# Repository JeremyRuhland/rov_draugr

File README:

5x h bridges
    4 input         =   20 input
                        3x 8-bit shift registers w/ spi interface
                                5 gpio: miso, mosi, sck, latch, cs
    1 output        =   5 outputs
    1 analog        =   5 analog
        
spi arm interface   =   spi interface
                        4 gpio: miso, mosi, sck, cs

conductivity sensor =   1 analog

temp sensing        =   4 analog

range finder        =   ? 
                        4 gpio

USB interface       =   1 input
                        1 interupt

-------------------------------------------------------------------------------

3 spi
2 uart for poolside comms: rx, tx
1 gpio for usb: +
1 interupt for usb: -
2 gpio for h bridge shift registers: latch, cs
5 gpio for h bridge status
5 adc for h bridge current draw
1 gpio for arm interface: cs
1 adc for water conductivity sensor
2 adc for heat pipe thermal monitors
?1 gpio for range finder: cs

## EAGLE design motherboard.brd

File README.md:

Western Washington University Marine Technology Club 2014 ROV: Draugr
=====================================================================

More information can be found on my [WWU MTC page](http://goopypanther.org/seniorProjectWebsite/wwu-marine-technology-club.html) or the [main blog post](http://blog.goopypanther.org/posts/ROV_Project:_Draugr/) about Draugr.

The stuff here's pretty old and probably doesn't reflect the current state of the ROV. Some firmware tweaks may have been made last minute in responce to hardware changes. Only the basic functionality was fully implemented and tested.

You can control the ROV via a screen session and the keyboard, the actual GUI that uses the xbox controller was written by Sean and got stored elsewhere (somewhere?).

File hierarchy
--------------

 * firmware
  * C source files
 * hardware
  * Schematics and gerbers for main control board
 * protocol_documentation
  * Command protocol for designing control software

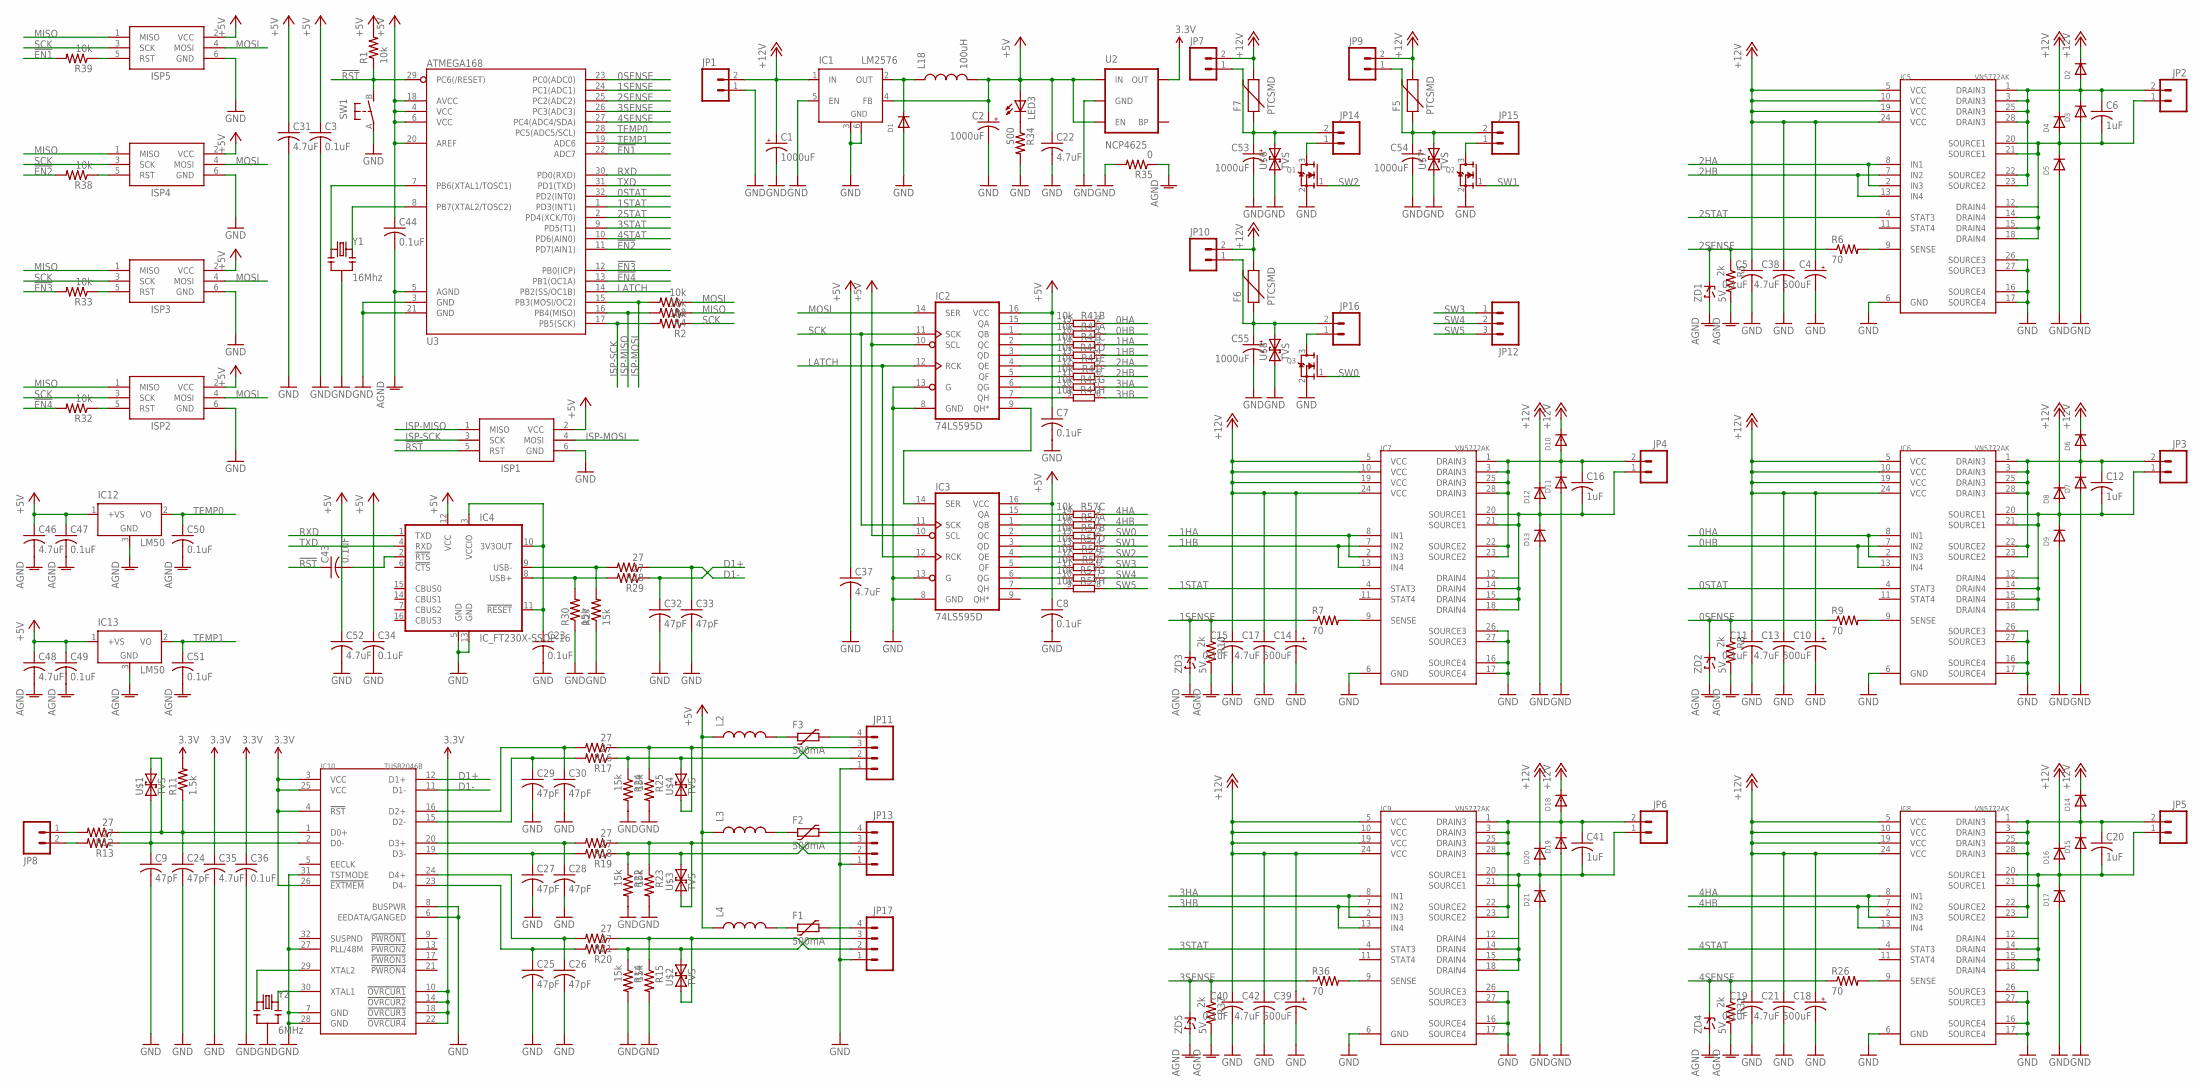
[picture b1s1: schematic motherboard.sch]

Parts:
C1, C2, C53, C54, C55: 1000uF; 153CLV-0807
C3, C5, C7, C8, C11, C15, C19, C23, C34, C36, C40, C43, C44, C47, C49, C50, C51: 0.1uF; C1206
C4, C10, C14, C18, C39: 500uF; 153CLV-0807
C6, C12, C16, C20, C41: 1uF; C1206
C9, C24, C25, C26, C27, C28, C29, C30, C32, C33: 47pF; C1206
C13, C17, C21, C22, C31, C35, C37, C38, C42, C46, C48, C52: 4.7uF; C1206
D1: DIODESMA; SMADIODE
D2, D3, D4, D5, D6, D7, D8, D9, D10, D11, D12, D13, D14, D15, D16, D17, D18, D19, D20, D21: DIODESOD-123; SOD-123
F1, F2, F3: 500mA; PTC1812L
F5, F6, F7: PTCSMD; PTC-1206
IC1: LM2576; TO263-5
IC2, IC3: 74LS595D; SO16
IC4: IC_FT230X-SSOP-16; SSOP-16-FTDI
IC5, IC6, IC7, IC8, IC9: VN5772AK; SO-28
IC10: TUSB2046B; LQFP-32
IC12, IC13: LM50; SOT23
ISP1, ISP2, ISP3, ISP4, ISP5: AVRISP-6; AVRISP
JP1, JP2, JP3, JP4, JP5, JP6, JP8, JP14, JP15, JP16: M023.5MM; SCREWTERMINAL-3.5MM-2
JP7, JP9, JP10: M02PTH; 1X02
JP11, JP13, JP17: M04SCREW; SCREWTERMINAL-3.5MM-4
JP12: M03PTH; 1X03
L2, L3, L4: INDUCTOR1206H*; INDUCTOR-1206
L18: 100uH; CDRH125
LED3: LEDCHIPLED_1206; CHIPLED_1206
Q1, Q2, Q3: MOSFET-NREFLOW; SOT23
R1, R2, R3, R4, R32, R33, R38, R39: 10k; R1206
R5, R8, R10, R31, R37: 2k; R1206
R6, R7, R9, R26, R36: 70; R1206
R11: 1.5k; R1206
R12, R13, R16, R17, R18, R19, R20, R21, R28, R29: 27; R1206
R14, R15, R22, R23, R24, R25, R27, R30: 15k; R1206
R34: 500; R1206
R35: 0; R1206
R41, R57: 10k; SO16
SW1: FSMSM
U2: NCP4625; SOT23-5
U3: ATMEGA168; TQFP32-08
U$1, U$2, U$3, U$4, U$6, U$7, U$8: TVS; SMA-DIODE
Y1: 16Mhz; RESONATOR-SMD
Y2: 6MHz; RESONATOR-SMD
ZD1, ZD2, ZD3, ZD4, ZD5: 5V; SOD-123

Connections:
0HA: IC6.2 (IN3), IC6.8 (IN1), R41.2 (1)
0HB: IC6.7 (IN2), IC6.13 (IN4), R41.1
0SENSE: R8.1, R9.1, U3.23 (PC0(ADC0)), ZD2.C
0STAT: IC6.4 (STAT3), U3.32 (PD2(INT0))
1HA: IC7.2 (IN3), IC7.8 (IN1), R41.3 (1)
1HB: IC7.7 (IN2), IC7.13 (IN4), R41.4 (1)
1SENSE: R7.1, R10.1, U3.24 (PC1(ADC1)), ZD3.C
1STAT: IC7.4 (STAT3), U3.1 (PD3(INT1))
2HA: IC5.2 (IN3), IC5.8 (IN1), R41.5 (1)
2HB: IC5.7 (IN2), IC5.13 (IN4), R41.6 (1)
2SENSE: R5.1, R6.1, U3.25 (PC2(ADC2)), ZD1.C
2STAT: IC5.4 (STAT3), U3.2 (PD4(XCK/T0))
3.3V: C35.1, C36.1, IC10.3 (VCC), IC10.4 (!RST), IC10.10 (!OVRCUR1), IC10.14 (!OVRCUR2), IC10.18 (!OVRCUR3), IC10.22 (!OVRCUR4), IC10.25 (VCC), IC10.26 (!EXTMEM), R11.2, U2.5 (OUT)
3HA: IC9.2 (IN3), IC9.8 (IN1), R41.7 (1)
3HB: IC9.7 (IN2), IC9.13 (IN4), R41.8 (1)
3SENSE: R36.1, R37.1, U3.26 (PC3(ADC3)), ZD5.C
3STAT: IC9.4 (STAT3), U3.9 (PD5(T1))
4HA: IC8.2 (IN3), IC8.8 (IN1), R57.3 (1)
4HB: IC8.7 (IN2), IC8.13 (IN4), R57.1
4SENSE: R26.1, R31.1, U3.27 (PC4(ADC4/SDA)), ZD4.C
4STAT: IC8.4 (STAT3), U3.10 (PD6(AIN0))
!EN1: R39.2, U3.22 (ADC7)
!EN2: R38.2, U3.11 (PD7(AIN1))
!EN3: R33.2, U3.12 (PB0(ICP))
!EN4: R32.2, U3.13 (PB1(OC1A))
!RST: C43.1, ISP1.5 (RST), R1.1, SW1.B (S), U3.29 (PC6(/RESET))
+5V: C2.+, C3.1, C7.1, C8.1, C22.1, C31.1, C34.1, C37.1, C44.1, C46.1, C47.1, C48.1, C49.1, C52.1, IC1.4 (FB), IC2.10 (SCL), IC2.16 (VCC), IC3.10 (SCL), IC3.16 (VCC), IC4.12 (VCC), IC12.1 (+VS), IC13.1 (+VS), ISP1.2 (VCC), ISP2.2 (VCC), ISP3.2 (VCC), ISP4.2 (VCC), ISP5.2 (VCC), L2.P$1 (1), L3.P$1 (1), L4.P$1 (1), L18.2, LED3.A, R1.2, U2.1 (IN), U2.3 (EN), U3.4 (VCC), U3.6 (VCC), U3.18 (AVCC), U3.20 (AREF)
+12V: C1.+, C4.+, C5.1, C10.+, C11.1, C13.1, C14.+, C15.1, C17.1, C18.+, C19.1, C21.1, C38.1, C39.+, C40.1, C42.1, D2.C, D4.C, D6.C, D8.C, D10.C, D12.C, D14.C, D16.C, D18.C, D20.C, F5.2, F6.2, F7.2, IC1.1 (IN), IC5.5 (VCC), IC5.10 (VCC), IC5.19 (VCC), IC5.24 (VCC), IC6.5 (VCC), IC6.10 (VCC), IC6.19 (VCC), IC6.24 (VCC), IC7.5 (VCC), IC7.10 (VCC), IC7.19 (VCC), IC7.24 (VCC), IC8.5 (VCC), IC8.10 (VCC), IC8.19 (VCC), IC8.24 (VCC), IC9.5 (VCC), IC9.10 (VCC), IC9.19 (VCC), IC9.24 (VCC), JP1.2, JP7.2, JP9.2, JP10.2; also elsewhere on the board
AGND: C44.2, C46.2, C47.2, C48.2, C49.2, C50.2, C51.2, IC12.3 (GND), IC13.3 (GND), R5.2, R8.2, R10.2, R31.2, R35.1, R37.2, U3.5 (AGND), ZD1.A, ZD2.A, ZD3.A, ZD4.A, ZD5.A
D1+: C32.1, IC10.12 (D1+), R29.1
D1-: C33.1, IC10.11 (D1-), R28.1
GND: C1.-, C2.-, C3.2, C4.-, C5.2, C7.2, C8.2, C9.2, C10.-, C11.2, C13.2, C14.-, C15.2, C17.2, C18.-, C19.2, C21.2, C22.2, C23.2, C24.2, C25.2, C26.2, C27.2, C28.2, C29.2, C30.2, C31.2, C32.2, C33.2, C34.2, C35.2, C36.2, C37.2, C38.2, C39.-, C40.2, C42.2, C52.2, C53.-, C54.-, C55.-, D1.A, D3.A, D5.A, D7.A, D9.A, D11.A, D13.A, D15.A, D17.A, D19.A, D21.A, IC1.3 (GND), IC1.5 (EN), IC1.6 (GND), IC2.8 (GND), IC2.13 (G), IC3.8 (GND), IC3.13 (G), IC4.5 (GND), IC4.13 (GND), IC5.6 (GND), IC5.16 (SOURCE4), IC5.17 (SOURCE4), IC5.26 (SOURCE3), IC5.27 (SOURCE3), IC6.6 (GND), IC6.16 (SOURCE4), IC6.17 (SOURCE4), IC6.26 (SOURCE3), IC6.27 (SOURCE3), IC7.6 (GND), IC7.16 (SOURCE4), IC7.17 (SOURCE4), IC7.26 (SOURCE3), IC7.27 (SOURCE3), IC8.6 (GND), IC8.16 (SOURCE4), IC8.17 (SOURCE4), IC8.26 (SOURCE3), IC8.27 (SOURCE3), IC9.6 (GND), IC9.16 (SOURCE4), IC9.17 (SOURCE4), IC9.26 (SOURCE3), IC9.27 (SOURCE3), IC10.6 (EEDATA/GANGED), IC10.7 (GND), IC10.8 (BUSPWR), IC10.27 (PLL/48M), IC10.28 (GND), IC10.31 (TSTMODE), ISP1.6 (GND), ISP2.6 (GND), ISP3.6 (GND), ISP4.6 (GND), ISP5.6 (GND), JP1.1, JP11.1, JP13.1, JP17.1, Q1.2 (S), Q2.2 (S), Q3.2 (S), R14.2, R15.2, R22.2, R23.2, R24.2, R25.2, R27.1, R30.1, R34.2, R35.2, SW1.A, U2.2 (GND), U3.3 (GND), U3.21 (GND), U$6.A (1), U$7.A (1), U$8.A (1), Y1.2, Y2.2
ISP-MISO: ISP1.1 (MISO), R4.2, U3.16 (PB4(MISO))
ISP-MOSI: ISP1.4 (MOSI), R3.2, U3.15 (PB3(MOSI/OC2))
ISP-SCK: ISP1.3 (SCK), R2.2, U3.17 (PB5(SCK))
LATCH: IC2.12 (RCK), IC3.12 (RCK), U3.14 (PB2(SS/OC1B))
MISO: ISP2.1 (MISO), ISP3.1 (MISO), ISP4.1 (MISO), ISP5.1 (MISO), R4.1
MOSI: IC2.14 (SER), ISP2.4 (MOSI), ISP3.4 (MOSI), ISP4.4 (MOSI), ISP5.4 (MOSI), R3.1
unnamed: D1.C, IC1.2 (OUT), L18.1
unnamed: U3.8 (PB7(XTAL2/TOSC2)), Y1.3
unnamed: C12.2, D8.A, D9.C, IC6.12 (DRAIN4), IC6.14 (DRAIN4), IC6.15 (DRAIN4), IC6.18 (DRAIN4), IC6.20 (SOURCE1), IC6.21 (SOURCE1), JP3.1
unnamed: U3.7 (PB6(XTAL1/TOSC1)), Y1.1
unnamed: C12.1, D6.A, D7.C, IC6.1 (DRAIN3), IC6.3 (DRAIN3), IC6.22 (SOURCE2), IC6.23 (SOURCE2), IC6.25 (DRAIN3), IC6.28 (DRAIN3), JP3.2
unnamed: IC2.9 (QH*), IC3.14 (SER)
unnamed: C9.1, IC10.2 (D0-), R13.1, U$1.A (1)
unnamed: C16.2, D12.A, D13.C, IC7.12 (DRAIN4), IC7.14 (DRAIN4), IC7.15 (DRAIN4), IC7.18 (DRAIN4), IC7.20 (SOURCE1), IC7.21 (SOURCE1), JP4.1
unnamed: C16.1, D10.A, D11.C, IC7.1 (DRAIN3), IC7.3 (DRAIN3), IC7.22 (SOURCE2), IC7.23 (SOURCE2), IC7.25 (DRAIN3), IC7.28 (DRAIN3), JP4.2
unnamed: C20.2, D16.A, D17.C, IC8.12 (DRAIN4), IC8.14 (DRAIN4), IC8.15 (DRAIN4), IC8.18 (DRAIN4), IC8.20 (SOURCE1), IC8.21 (SOURCE1), JP5.1
unnamed: C20.1, D14.A, D15.C, IC8.1 (DRAIN3), IC8.3 (DRAIN3), IC8.22 (SOURCE2), IC8.23 (SOURCE2), IC8.25 (DRAIN3), IC8.28 (DRAIN3), JP5.2
unnamed: C41.2, D20.A, D21.C, IC9.12 (DRAIN4), IC9.14 (DRAIN4), IC9.15 (DRAIN4), IC9.18 (DRAIN4), IC9.20 (SOURCE1), IC9.21 (SOURCE1), JP6.1
unnamed: C6.2, D4.A, D5.C, IC5.12 (DRAIN4), IC5.14 (DRAIN4), IC5.15 (DRAIN4), IC5.18 (DRAIN4), IC5.20 (SOURCE1), IC5.21 (SOURCE1), JP2.1
unnamed: C41.1, D18.A, D19.C, IC9.1 (DRAIN3), IC9.3 (DRAIN3), IC9.22 (SOURCE2), IC9.23 (SOURCE2), IC9.25 (DRAIN3), IC9.28 (DRAIN3), JP6.2
unnamed: IC3.7 (QH), R57.9 (2)
unnamed: C43.2, IC4.2 (!RTS)
unnamed: IC3.6 (QG), R57.10 (2)
unnamed: IC3.5 (QF), R57.11 (2)
unnamed: C24.1, IC10.1 (D0+), R11.1, R12.1, U$1.C (2)
unnamed: JP17.2, R15.1, R21.1, U$2.A (1)
unnamed: IC10.30 (XTAL1), Y2.3
unnamed: IC10.29 (XTAL2), Y2.1
unnamed: JP17.3, R14.1, R20.1, U$2.C (2)
unnamed: JP13.3, R19.1, R22.1, U$3.C (2)
unnamed: C30.1, IC10.16 (D2+), R16.2
unnamed: C29.1, IC10.15 (D2-), R17.2
unnamed: C28.1, IC10.20 (D3+), R18.2
unnamed: C27.1, IC10.19 (D3-), R19.2
unnamed: C25.1, IC10.23 (D4-), R20.2
unnamed: C26.1, IC10.24 (D4+), R21.2
unnamed: JP13.2, R18.1, R23.1, U$3.A (1)
unnamed: JP11.3, R17.1, R24.1, U$4.C (2)
unnamed: JP11.2, R16.1, R25.1, U$4.A (1)
unnamed: F1.2, JP17.4
unnamed: F2.2, JP13.4
unnamed: F3.2, JP11.4
unnamed: C23.1, IC4.3 (VCCIO), IC4.10 (3V3OUT), IC4.11 (!RESET)
unnamed: IC4.9 (USB-), R27.2, R28.2
unnamed: IC4.8 (USB+), R29.2, R30.2
unnamed: F3.1, L2.P$2 (2)
unnamed: F2.1, L3.P$2 (2)
unnamed: JP14.1, Q1.3 (D)
unnamed: JP8.1, R12.2
unnamed: JP8.2, R13.2
unnamed: LED3.C, R34.1
unnamed: JP15.1, Q2.3 (D)
unnamed: JP16.1, Q3.3 (D)
unnamed: F1.1, L4.P$2 (2)
unnamed 89: C55.+, F6.1, JP10.1, JP16.2, U$8.C (2); also elsewhere on the board
unnamed: ISP2.5 (RST), R32.1
unnamed: ISP3.5 (RST), R33.1
unnamed: ISP4.5 (RST), R38.1
unnamed 93: C54.+, F5.1, JP9.1, JP15.2, U$7.C (2); also elsewhere on the board
unnamed 94: C53.+, F7.1, JP7.1, JP14.2, U$6.C (2); also elsewhere on the board
unnamed: IC3.4 (QE), R57.12 (2)
unnamed: ISP5.5 (RST), R39.1
unnamed: C6.1, D2.A, D3.C, IC5.1 (DRAIN3), IC5.3 (DRAIN3), IC5.22 (SOURCE2), IC5.23 (SOURCE2), IC5.25 (DRAIN3), IC5.28 (DRAIN3), JP2.2
unnamed: IC3.3 (QD), R57.13 (2)
unnamed: IC3.2 (QC), R57.15 (2)
unnamed: IC3.1 (QB), R57.16 (2)
unnamed: IC3.15 (QA), R57.14 (2)
unnamed: IC2.7 (QH), R41.9 (2)
unnamed: IC2.6 (QG), R41.10 (2)
unnamed: IC2.5 (QF), R41.11 (2)
unnamed: IC2.4 (QE), R41.12 (2)
unnamed: IC2.3 (QD), R41.13 (2)
unnamed: IC2.2 (QC), R41.14 (2)
unnamed: IC2.1 (QB), R41.16 (2)
unnamed: IC2.15 (QA), R41.15 (2)
unnamed: IC5.9 (SENSE), R6.2
unnamed: IC7.9 (SENSE), R7.2
unnamed: IC6.9 (SENSE), R9.2
unnamed: IC9.9 (SENSE), R36.2
unnamed: IC8.9 (SENSE), R26.2
RXD: IC4.1 (TXD), U3.30 (PD0(RXD))
SCK: IC2.11 (SCK), IC3.11 (SCK), ISP2.3 (SCK), ISP3.3 (SCK), ISP4.3 (SCK), ISP5.3 (SCK), R2.1
SW0: Q3.1 (G), R57.2 (1)
SW1: Q2.1 (G), R57.4 (1)
SW2: Q1.1 (G), R57.5 (1)
SW3: JP12.1, R57.6 (1)
SW4: JP12.2, R57.7 (1)
SW5: JP12.3, R57.8 (1)
TEMP0: C50.1, IC12.2 (VO), U3.28 (PC5(ADC5/SCL))
TEMP1: C51.1, IC13.2 (VO), U3.19 (ADC6)
TXD: IC4.4 (RXD), U3.31 (PD1(TXD))

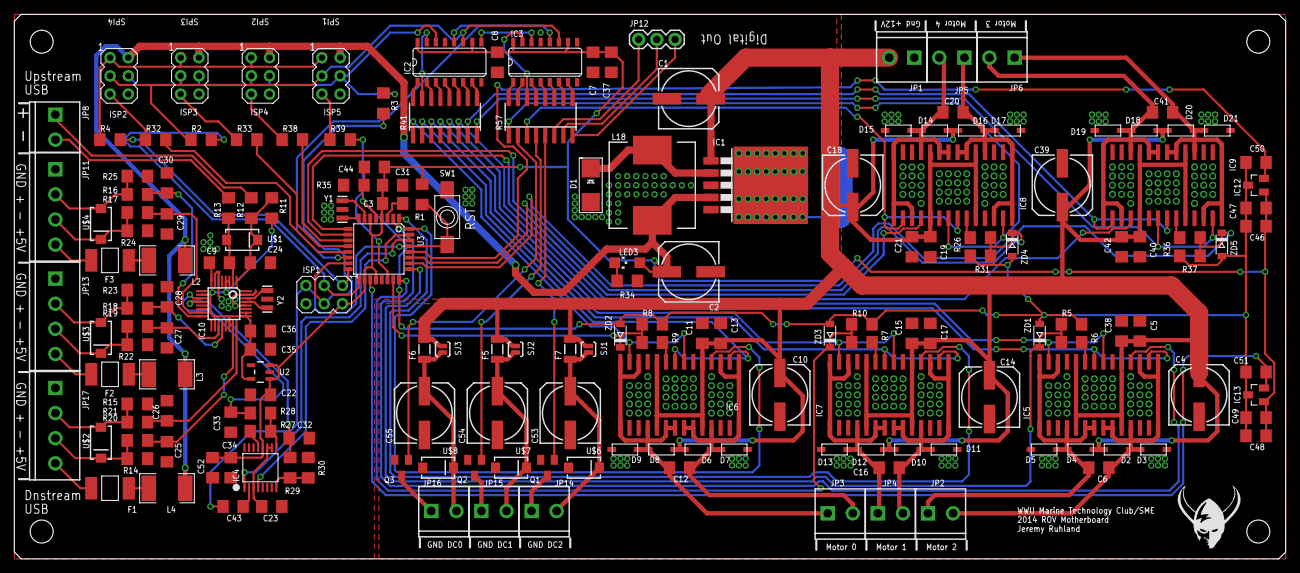
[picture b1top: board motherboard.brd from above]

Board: 2 copper layers, 177.2 x 75.9 mm, 181 parts (0 on the bottom side), 123 nets.

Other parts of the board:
SJ1, SJ2, SJ3: JMP; SJ_2S-NO

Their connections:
+12V: SJ1.2, SJ2.2, SJ3.2; also elsewhere on the board
unnamed 89: SJ3.1; also elsewhere on the board
unnamed 93: SJ2.1; also elsewhere on the board
unnamed 94: SJ1.1; also elsewhere on the board

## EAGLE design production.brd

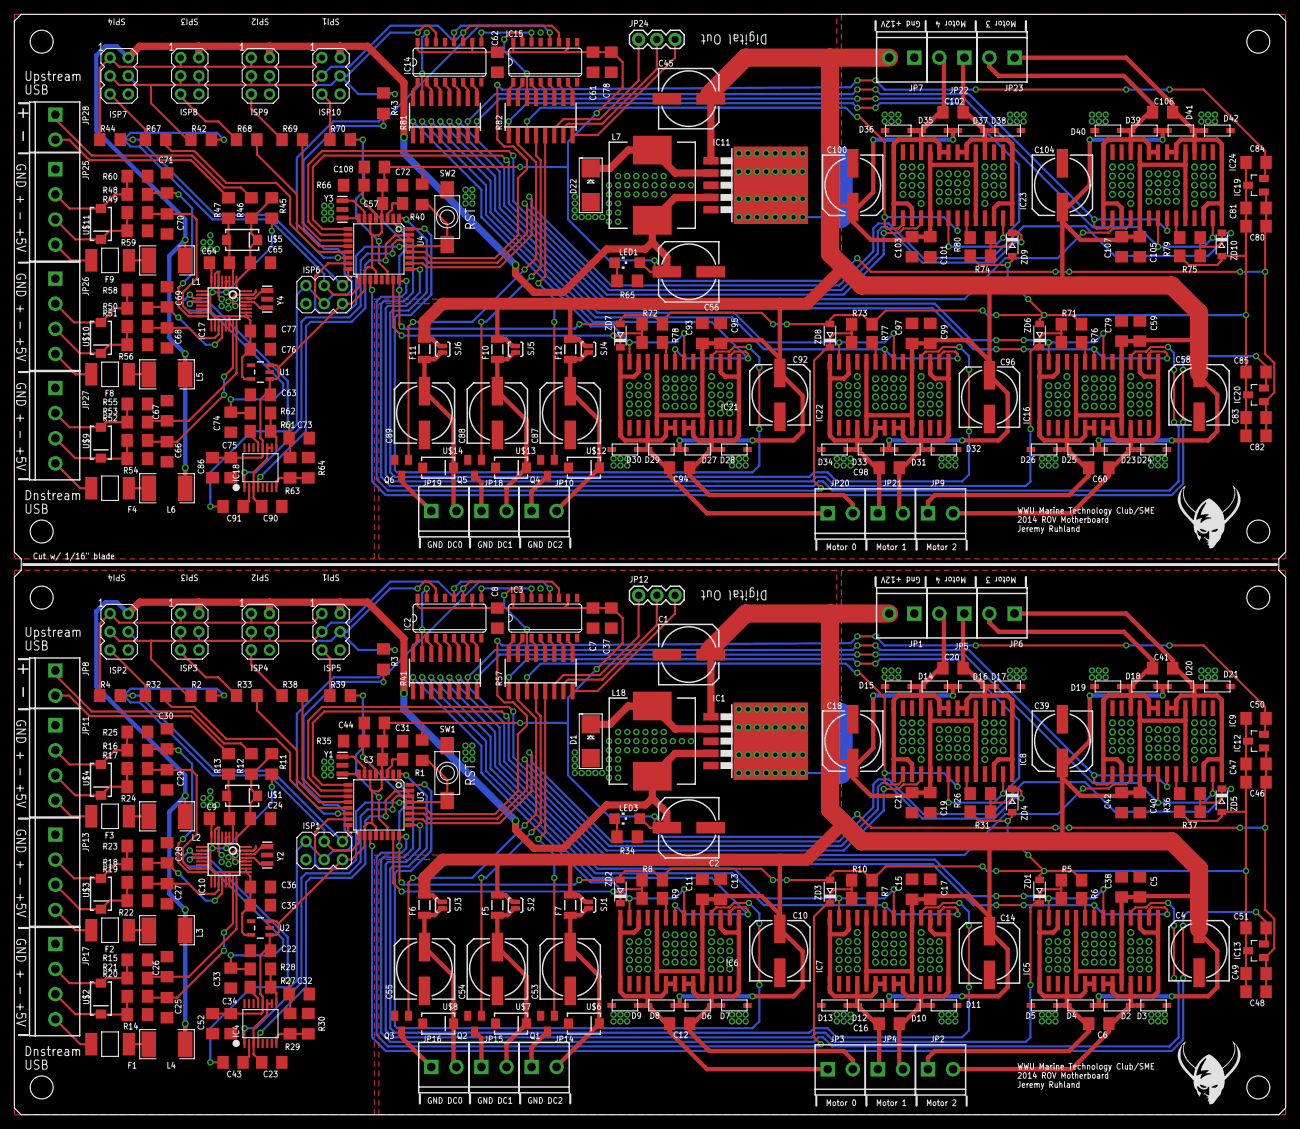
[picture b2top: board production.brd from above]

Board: 2 copper layers, 177.2 x 153.4 mm, 362 parts (0 on the bottom side), 246 nets.

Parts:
C1, C2, C45, C53, C54, C55, C56, C87, C88, C89: 1000uF; 153CLV-0807
C3, C5, C7, C8, C11, C15, C19, C23, C34, C36, C40, C43, C44, C47, C49, C50, C51, C57, C59, C61, C62, C75, C77, C81, C83, C84, C85, C90, C91, C93, C97, C101, C105, C108: 0.1uF; C1206
C4, C10, C14, C18, C39, C58, C92, C96, C100, C104: 500uF; 153CLV-0807
C6, C12, C16, C20, C41, C60, C94, C98, C102, C106: 1uF; C1206
C9, C24, C25, C26, C27, C28, C29, C30, C32, C33, C64, C65, C66, C67, C68, C69, C70, C71, C73, C74: 47pF; C1206
C13, C17, C21, C22, C31, C35, C37, C38, C42, C46, C48, C52, C63, C72, C76, C78, C79, C80, C82, C86, C95, C99, C103, C107: 4.7uF; C1206
D1, D22: SMADIODE
D2, D3, D4, D5, D6, D7, D8, D9, D10, D11, D12, D13, D14, D15, D16, D17, D18, D19, D20, D21, D23, D24, D25, D26, D27, D28, D29, D30, D31, D32, D33, D34, D35, D36, D37, D38, D39, D40, D41, D42: SOD-123
F1, F2, F3, F4, F8, F9: 500mA; PTC1812L
F5, F6, F7, F10, F11, F12: PTCSMD; PTC-1206
IC1, IC11: LM2576; TO263-5
IC2, IC3, IC14, IC15: 74LS595D; SO16
IC4, IC18: IC_FT230X-SSOP-16; SSOP-16-FTDI
IC5, IC6, IC7, IC8, IC9, IC16, IC21, IC22, IC23, IC24: VN5772AK; SO-28
IC10, IC17: TUSB2046B; LQFP-32
IC12, IC13, IC19, IC20: LM50; SOT23
ISP1, ISP2, ISP3, ISP4, ISP5, ISP6, ISP7, ISP8, ISP9, ISP10: AVRISP-6; AVRISP
JP1, JP2, JP3, JP4, JP5, JP6, JP7, JP8, JP9, JP10, JP14, JP15, JP16, JP18, JP19, JP20, JP21, JP22, JP23, JP28: SCREWTERMINAL-3.5MM-2
JP11, JP13, JP17, JP25, JP26, JP27: SCREWTERMINAL-3.5MM-4
JP12, JP24: 1X03
L1, L2, L3, L4, L5, L6: INDUCTOR-1206
L7, L18: 100uH; CDRH125
LED1, LED3: CHIPLED_1206
Q1, Q2, Q3, Q4, Q5, Q6: SOT23
R1, R2, R3, R4, R32, R33, R38, R39, R40, R42, R43, R44, R67, R68, R69, R70: 10k; R1206
R5, R8, R10, R31, R37, R71, R72, R73, R74, R75: 2k; R1206
R6, R7, R9, R26, R36, R76, R77, R78, R79, R80: 70; R1206
R11, R45: 1.5k; R1206
R12, R13, R16, R17, R18, R19, R20, R21, R28, R29, R46, R47, R48, R49, R50, R51, R52, R53, R62, R63: 27; R1206
R14, R15, R22, R23, R24, R25, R27, R30, R54, R55, R56, R58, R59, R60, R61, R64: 15k; R1206
R34, R65: 500; R1206
R35, R66: 0; R1206
R41, R57, R81, R82: 10k; SO16
SJ1, SJ2, SJ3, SJ4, SJ5, SJ6: JMP; SJ_2S-NO
SW1, SW2: FSMSM
U1, U2: NCP4625; SOT23-5
U3, U4: ATMEGA168; TQFP32-08
U$1, U$2, U$3, U$4, U$5, U$6, U$7, U$8, U$9, U$10, U$11, U$12, U$13, U$14: TVS; SMA-DIODE
Y1, Y3: 16Mhz; RESONATOR-SMD
Y2, Y4: 6MHz; RESONATOR-SMD
ZD1, ZD2, ZD3, ZD4, ZD5, ZD6, ZD7, ZD8, ZD9, ZD10: 5V; SOD-123

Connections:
0HA: IC6.2, IC6.8, R41.2
0HA1: IC21.2, IC21.8, R81.2
0HB: IC6.7, IC6.13, R41.1
0HB1: IC21.7, IC21.13, R81.1
0SENSE: R8.1, R9.1, U3.23, ZD2.C
0SENSE1: R72.1, R78.1, U4.23, ZD7.C
0STAT: IC6.4, U3.32
0STAT1: IC21.4, U4.32
1HA: IC7.2, IC7.8, R41.3
1HA1: IC22.2, IC22.8, R81.3
1HB: IC7.7, IC7.13, R41.4
1HB1: IC22.7, IC22.13, R81.4
1SENSE: R7.1, R10.1, U3.24, ZD3.C
1SENSE1: R73.1, R77.1, U4.24, ZD8.C
1STAT: IC7.4, U3.1
1STAT1: IC22.4, U4.1
2HA: IC5.2, IC5.8, R41.5
2HA1: IC16.2, IC16.8, R81.5
2HB: IC5.7, IC5.13, R41.6
2HB1: IC16.7, IC16.13, R81.6
2SENSE: R5.1, R6.1, U3.25, ZD1.C
2SENSE1: R71.1, R76.1, U4.25, ZD6.C
2STAT: IC5.4, U3.2
2STAT1: IC16.4, U4.2
3.3V: C35.1, C36.1, IC10.3, IC10.4, IC10.10, IC10.14, IC10.18, IC10.22, IC10.25, IC10.26, R11.2, U2.5
3.3V1: C76.1, C77.1, IC17.3, IC17.4, IC17.10, IC17.14, IC17.18, IC17.22, IC17.25, IC17.26, R45.2, U1.5
3HA: IC9.2, IC9.8, R41.7
3HA1: IC24.2, IC24.8, R81.7
3HB: IC9.7, IC9.13, R41.8
3HB1: IC24.7, IC24.13, R81.8
3SENSE: R36.1, R37.1, U3.26, ZD5.C
3SENSE1: R75.1, R79.1, U4.26, ZD10.C
3STAT: IC9.4, U3.9
3STAT1: IC24.4, U4.9
4HA: IC8.2, IC8.8, R57.3
4HA1: IC23.2, IC23.8, R82.3
4HB: IC8.7, IC8.13, R57.1
4HB1: IC23.7, IC23.13, R82.1
4SENSE: R26.1, R31.1, U3.27, ZD4.C
4SENSE1: R74.1, R80.1, U4.27, ZD9.C
4STAT: IC8.4, U3.10
4STAT1: IC23.4, U4.10
!EN1: R39.2, U3.22
!EN2: R38.2, U3.11
!EN3: R33.2, U3.12
!EN4: R32.2, U3.13
!EN5: R67.2, U4.13
!EN6: R68.2, U4.12
!EN7: R70.2, U4.22
!EN8: R69.2, U4.11
!RST: C43.1, ISP1.5, R1.1, SW1.B, U3.29
!RST1: C91.1, ISP6.5, R40.1, SW2.B, U4.29
+5V: C2.+, C3.1, C7.1, C8.1, C22.1, C31.1, C34.1, C37.1, C44.1, C46.1, C47.1, C48.1, C49.1, C52.1, IC1.4, IC2.10, IC2.16, IC3.10, IC3.16, IC4.12, IC12.1, IC13.1, ISP1.2, ISP2.2, ISP3.2, ISP4.2, ISP5.2, L2.P$1, L3.P$1, L4.P$1, L18.2, LED3.A, R1.2, U2.1, U2.3, U3.4, U3.6, U3.18, U3.20
+5V1: C56.+, C57.1, C61.1, C62.1, C63.1, C72.1, C75.1, C78.1, C80.1, C81.1, C82.1, C83.1, C86.1, C108.1, IC11.4, IC14.10, IC14.16, IC15.10, IC15.16, IC18.12, IC19.1, IC20.1, ISP6.2, ISP7.2, ISP8.2, ISP9.2, ISP10.2, L1.P$1, L5.P$1, L6.P$1, L7.2, LED1.A, R40.2, U1.1, U1.3, U4.4, U4.6, U4.18, U4.20
+12V: C1.+, C4.+, C5.1, C10.+, C11.1, C13.1, C14.+, C15.1, C17.1, C18.+, C19.1, C21.1, C38.1, C39.+, C40.1, C42.1, D2.C, D4.C, D6.C, D8.C, D10.C, D12.C, D14.C, D16.C, D18.C, D20.C, F5.2, F6.2, F7.2, IC1.1, IC5.5, IC5.10, IC5.19, IC5.24, IC6.5, IC6.10, IC6.19, IC6.24, IC7.5, IC7.10, IC7.19, IC7.24, IC8.5, IC8.10, IC8.19, IC8.24, IC9.5, IC9.10, IC9.19, IC9.24, JP1.2, SJ1.2, SJ2.2, SJ3.2
+12V1: C45.+, C58.+, C59.1, C79.1, C92.+, C93.1, C95.1, C96.+, C97.1, C99.1, C100.+, C101.1, C103.1, C104.+, C105.1, C107.1, D23.C, D25.C, D27.C, D29.C, D31.C, D33.C, D35.C, D37.C, D39.C, D41.C, F10.2, F11.2, F12.2, IC11.1, IC16.5, IC16.10, IC16.19, IC16.24, IC21.5, IC21.10, IC21.19, IC21.24, IC22.5, IC22.10, IC22.19, IC22.24, IC23.5, IC23.10, IC23.19, IC23.24, IC24.5, IC24.10, IC24.19, IC24.24, JP7.2, SJ4.2, SJ5.2, SJ6.2
AGND: C44.2, C46.2, C47.2, C48.2, C49.2, C50.2, C51.2, IC12.3, IC13.3, R5.2, R8.2, R10.2, R31.2, R35.1, R37.2, U3.5, ZD1.A, ZD2.A, ZD3.A, ZD4.A, ZD5.A
AGND1: C80.2, C81.2, C82.2, C83.2, C84.2, C85.2, C108.2, IC19.3, IC20.3, R66.1, R71.2, R72.2, R73.2, R74.2, R75.2, U4.5, ZD6.A, ZD7.A, ZD8.A, ZD9.A, ZD10.A
D1+: C32.1, IC10.12, R29.1
D1+1: C73.1, IC17.12, R63.1
D1-: C33.1, IC10.11, R28.1
D1-1: C74.1, IC17.11, R62.1
GND: C1.-, C2.-, C3.2, C4.-, C5.2, C7.2, C8.2, C9.2, C10.-, C11.2, C13.2, C14.-, C15.2, C17.2, C18.-, C19.2, C21.2, C22.2, C23.2, C24.2, C25.2, C26.2, C27.2, C28.2, C29.2, C30.2, C31.2, C32.2, C33.2, C34.2, C35.2, C36.2, C37.2, C38.2, C39.-, C40.2, C42.2, C52.2, C53.-, C54.-, C55.-, D1.A, D3.A, D5.A, D7.A, D9.A, D11.A, D13.A, D15.A, D17.A, D19.A, D21.A, IC1.3, IC1.5, IC1.6, IC2.8, IC2.13, IC3.8, IC3.13, IC4.5, IC4.13, IC5.6, IC5.16, IC5.17, IC5.26, IC5.27, IC6.6, IC6.16, IC6.17, IC6.26, IC6.27, IC7.6, IC7.16, IC7.17, IC7.26, IC7.27, IC8.6, IC8.16, IC8.17, IC8.26, IC8.27, IC9.6, IC9.16, IC9.17, IC9.26, IC9.27, IC10.6, IC10.7, IC10.8, IC10.27, IC10.28, IC10.31, ISP1.6, ISP2.6, ISP3.6, ISP4.6, ISP5.6, JP1.1, JP11.1, JP13.1, JP17.1, Q1.2, Q2.2, Q3.2, R14.2, R15.2, R22.2, R23.2, R24.2, R25.2, R27.1, R30.1, R34.2, R35.2, SW1.A, U2.2, U3.3, U3.21, U$6.A, U$7.A, U$8.A, Y1.2, Y2.2
GND1: C45.-, C56.-, C57.2, C58.-, C59.2, C61.2, C62.2, C63.2, C64.2, C65.2, C66.2, C67.2, C68.2, C69.2, C70.2, C71.2, C72.2, C73.2, C74.2, C75.2, C76.2, C77.2, C78.2, C79.2, C86.2, C87.-, C88.-, C89.-, C90.2, C92.-, C93.2, C95.2, C96.-, C97.2, C99.2, C100.-, C101.2, C103.2, C104.-, C105.2, C107.2, D22.A, D24.A, D26.A, D28.A, D30.A, D32.A, D34.A, D36.A, D38.A, D40.A, D42.A, IC11.3, IC11.5, IC11.6, IC14.8, IC14.13, IC15.8, IC15.13, IC16.6, IC16.16, IC16.17, IC16.26, IC16.27, IC17.6, IC17.7, IC17.8, IC17.27, IC17.28, IC17.31, IC18.5, IC18.13, IC21.6, IC21.16, IC21.17, IC21.26, IC21.27, IC22.6, IC22.16, IC22.17, IC22.26, IC22.27, IC23.6, IC23.16, IC23.17, IC23.26, IC23.27, IC24.6, IC24.16, IC24.17, IC24.26, IC24.27, ISP6.6, ISP7.6, ISP8.6, ISP9.6, ISP10.6, JP7.1, JP25.1, JP26.1, JP27.1, Q4.2, Q5.2, Q6.2, R54.2, R55.2, R56.2, R58.2, R59.2, R60.2, R61.1, R64.1, R65.2, R66.2, SW2.A, U1.2, U4.3, U4.21, U$12.A, U$13.A, U$14.A, Y3.2, Y4.2
ISP-MISO: ISP1.1, R4.2, U3.16
ISP-MISO1: ISP6.1, R44.2, U4.16
ISP-MOSI: ISP1.4, R3.2, U3.15
ISP-MOSI1: ISP6.4, R43.2, U4.15
ISP-SCK: ISP1.3, R2.2, U3.17
ISP-SCK1: ISP6.3, R42.2, U4.17
LATCH: IC2.12, IC3.12, U3.14
LATCH1: IC14.12, IC15.12, U4.14
MISO: ISP2.1, ISP3.1, ISP4.1, ISP5.1, R4.1
MISO1: ISP7.1, ISP8.1, ISP9.1, ISP10.1, R44.1
MOSI: IC2.14, ISP2.4, ISP3.4, ISP4.4, ISP5.4, R3.1
MOSI1: IC14.14, ISP7.4, ISP8.4, ISP9.4, ISP10.4, R43.1
unnamed: D1.C, IC1.2, L18.1
unnamed: U3.8, Y1.3
unnamed: C12.2, D8.A, D9.C, IC6.12, IC6.14, IC6.15, IC6.18, IC6.20, IC6.21, JP3.1
unnamed: U3.7, Y1.1
unnamed: C12.1, D6.A, D7.C, IC6.1, IC6.3, IC6.22, IC6.23, IC6.25, IC6.28, JP3.2
unnamed: IC2.9, IC3.14
unnamed: C9.1, IC10.2, R13.1, U$1.A
unnamed: C16.2, D12.A, D13.C, IC7.12, IC7.14, IC7.15, IC7.18, IC7.20, IC7.21, JP4.1
unnamed: C16.1, D10.A, D11.C, IC7.1, IC7.3, IC7.22, IC7.23, IC7.25, IC7.28, JP4.2
unnamed: C20.2, D16.A, D17.C, IC8.12, IC8.14, IC8.15, IC8.18, IC8.20, IC8.21, JP5.1
unnamed: C20.1, D14.A, D15.C, IC8.1, IC8.3, IC8.22, IC8.23, IC8.25, IC8.28, JP5.2
unnamed: C41.2, D20.A, D21.C, IC9.12, IC9.14, IC9.15, IC9.18, IC9.20, IC9.21, JP6.1
unnamed: C6.2, D4.A, D5.C, IC5.12, IC5.14, IC5.15, IC5.18, IC5.20, IC5.21, JP2.1
unnamed: C41.1, D18.A, D19.C, IC9.1, IC9.3, IC9.22, IC9.23, IC9.25, IC9.28, JP6.2
unnamed: IC3.7, R57.9
unnamed: C43.2, IC4.2
unnamed: IC3.6, R57.10
unnamed: IC3.5, R57.11
unnamed: C24.1, IC10.1, R11.1, R12.1, U$1.C
unnamed: D22.C, IC11.2, L7.1
unnamed: JP17.2, R15.1, R21.1, U$2.A
unnamed: IC10.30, Y2.3
unnamed: IC10.29, Y2.1
unnamed: JP17.3, R14.1, R20.1, U$2.C
unnamed: JP13.3, R19.1, R22.1, U$3.C
unnamed: C30.1, IC10.16, R16.2
unnamed: C29.1, IC10.15, R17.2
unnamed: C28.1, IC10.20, R18.2
unnamed: C27.1, IC10.19, R19.2
unnamed: C25.1, IC10.23, R20.2
unnamed: C26.1, IC10.24, R21.2
unnamed: JP13.2, R18.1, R23.1, U$3.A
unnamed: JP11.3, R17.1, R24.1, U$4.C
unnamed: JP11.2, R16.1, R25.1, U$4.A
unnamed: F1.2, JP17.4
unnamed: F2.2, JP13.4
unnamed: F3.2, JP11.4
unnamed: C23.1, IC4.3, IC4.10, IC4.11
unnamed: IC4.9, R27.2, R28.2
unnamed: IC4.8, R29.2, R30.2
unnamed: F3.1, L2.P$2
unnamed: F2.1, L3.P$2
unnamed: JP14.1, Q1.3
unnamed: JP8.1, R12.2
unnamed: JP8.2, R13.2
unnamed: LED3.C, R34.1
unnamed: JP15.1, Q2.3
unnamed: JP16.1, Q3.3
unnamed: F1.1, L4.P$2
unnamed: C55.+, F6.1, JP16.2, SJ3.1, U$8.C
unnamed: ISP2.5, R32.1
unnamed: ISP3.5, R33.1
unnamed: ISP4.5, R38.1
unnamed: C54.+, F5.1, JP15.2, SJ2.1, U$7.C
unnamed: C53.+, F7.1, JP14.2, SJ1.1, U$6.C
unnamed: IC3.4, R57.12
unnamed: IC14.9, IC15.14
unnamed: ISP5.5, R39.1
unnamed: C6.1, D2.A, D3.C, IC5.1, IC5.3, IC5.22, IC5.23, IC5.25, IC5.28, JP2.2
unnamed: IC3.3, R57.13
unnamed: IC3.2, R57.15
unnamed: IC3.1, R57.16
unnamed: IC3.15, R57.14
unnamed: IC2.7, R41.9
unnamed: IC2.6, R41.10
unnamed: IC2.5, R41.11
unnamed: IC2.4, R41.12
unnamed: IC2.3, R41.13
unnamed: IC2.2, R41.14
unnamed: IC2.1, R41.16
unnamed: IC2.15, R41.15
unnamed: C60.2, D25.A, D26.C, IC16.12, IC16.14, IC16.15, IC16.18, IC16.20, IC16.21, JP9.1
unnamed: C64.1, IC17.2, R47.1, U$5.A
unnamed: C65.1, IC17.1, R45.1, R46.1, U$5.C
unnamed: IC17.30, Y4.3
unnamed: IC5.9, R6.2
unnamed: IC7.9, R7.2
unnamed: IC6.9, R9.2
unnamed: IC9.9, R36.2
unnamed: IC8.9, R26.2
unnamed: IC17.29, Y4.1
unnamed: C71.1, IC17.16, R48.2
unnamed: C70.1, IC17.15, R49.2
unnamed: C69.1, IC17.20, R50.2
unnamed: C68.1, IC17.19, R51.2
unnamed: C66.1, IC17.23, R52.2
unnamed: C67.1, IC17.24, R53.2
unnamed: JP27.2, R53.1, R55.1, U$9.A
unnamed: JP27.3, R52.1, R54.1, U$9.C
unnamed: JP26.3, R51.1, R56.1, U$10.C
unnamed: JP26.2, R50.1, R58.1, U$10.A
unnamed: JP25.3, R49.1, R59.1, U$11.C
unnamed: JP25.2, R48.1, R60.1, U$11.A
unnamed: F4.2, JP27.4
unnamed: F8.2, JP26.4
unnamed: F9.2, JP25.4
unnamed: JP28.1, R46.2
unnamed: JP28.2, R47.2
unnamed: U4.8, Y3.3
unnamed: U4.7, Y3.1
unnamed: C90.1, IC18.3, IC18.10, IC18.11
unnamed: IC18.9, R61.2, R62.2
unnamed: IC18.8, R63.2, R64.2
unnamed: F9.1, L1.P$2
unnamed: F8.1, L5.P$2
unnamed: F4.1, L6.P$2
unnamed: JP10.1, Q4.3
unnamed: JP18.1, Q5.3
unnamed: JP19.1, Q6.3
unnamed: LED1.C, R65.1
unnamed: ISP7.5, R67.1
unnamed: ISP8.5, R68.1
unnamed: ISP9.5, R69.1
unnamed: ISP10.5, R70.1
unnamed: C89.+, F11.1, JP19.2, SJ6.1, U$14.C
unnamed: C88.+, F10.1, JP18.2, SJ5.1, U$13.C
unnamed: C87.+, F12.1, JP10.2, SJ4.1, U$12.C
unnamed: C91.2, IC18.2
unnamed: C60.1, D23.A, D24.C, IC16.1, IC16.3, IC16.22, IC16.23, IC16.25, IC16.28, JP9.2
unnamed: C94.2, D29.A, D30.C, IC21.12, IC21.14, IC21.15, IC21.18, IC21.20, IC21.21, JP20.1
unnamed: C94.1, D27.A, D28.C, IC21.1, IC21.3, IC21.22, IC21.23, IC21.25, IC21.28, JP20.2
unnamed: C98.2, D33.A, D34.C, IC22.12, IC22.14, IC22.15, IC22.18, IC22.20, IC22.21, JP21.1
unnamed: C98.1, D31.A, D32.C, IC22.1, IC22.3, IC22.22, IC22.23, IC22.25, IC22.28, JP21.2
unnamed: C102.2, D37.A, D38.C, IC23.12, IC23.14, IC23.15, IC23.18, IC23.20, IC23.21, JP22.1
unnamed: C102.1, D35.A, D36.C, IC23.1, IC23.3, IC23.22, IC23.23, IC23.25, IC23.28, JP22.2
unnamed: C106.2, D41.A, D42.C, IC24.12, IC24.14, IC24.15, IC24.18, IC24.20, IC24.21, JP23.1
unnamed: C106.1, D39.A, D40.C, IC24.1, IC24.3, IC24.22, IC24.23, IC24.25, IC24.28, JP23.2
unnamed: IC15.7, R82.9
unnamed: IC15.6, R82.10
unnamed: IC15.5, R82.11
unnamed: IC15.4, R82.12
unnamed: IC15.3, R82.13
unnamed: IC15.2, R82.15
unnamed: IC15.1, R82.16
unnamed: IC15.15, R82.14
unnamed: IC14.7, R81.9
unnamed: IC14.6, R81.10
unnamed: IC14.5, R81.11
unnamed: IC14.4, R81.12
unnamed: IC14.3, R81.13
unnamed: IC14.2, R81.14
unnamed: IC14.1, R81.16
unnamed: IC14.15, R81.15
unnamed: IC16.9, R76.2
unnamed: IC22.9, R77.2
unnamed: IC21.9, R78.2
unnamed: IC24.9, R79.2
unnamed: IC23.9, R80.2
RXD: IC4.1, U3.30
RXD1: IC18.1, U4.30
SCK: IC2.11, IC3.11, ISP2.3, ISP3.3, ISP4.3, ISP5.3, R2.1
SCK1: IC14.11, IC15.11, ISP7.3, ISP8.3, ISP9.3, ISP10.3, R42.1
SW0: Q3.1, R57.2
SW1: Q2.1, R57.4
SW2: Q1.1, R57.5
SW3: JP12.1, R57.6
SW4: JP12.2, R57.7
SW5: JP12.3, R57.8
SW6: JP24.1, R82.6
SW7: Q4.1, R82.5
SW8: Q5.1, R82.4
SW9: Q6.1, R82.2
SW10: JP24.3, R82.8
SW11: JP24.2, R82.7
TEMP0: C50.1, IC12.2, U3.28
TEMP1: C51.1, IC13.2, U3.19
TEMP2: C84.1, IC19.2, U4.28
TEMP3: C85.1, IC20.2, U4.19
TXD: IC4.4, U3.31
TXD1: IC18.4, U4.31

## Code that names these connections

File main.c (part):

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
void initGpio(void) {
    // Set all chip select lines high to disable peripherals on startup
    PORTD |= (1<<PD7);
    DDRD |= ((1<<PD1) | (1<<PD7));

    PORTC |= (1<<PC5);
    DDRC |= (1<<PC5);

    PORTB |= ((0<<PB0) | (1<<PB1)); // Set PB0 back to output after testing
    DDRB |= ((0<<PB0) | (1<<PB1) | (1<<PB2) | (1<<PB3) | (1<<PB5)); // Set PB0 back to output after testing
}

void runCommand(void) {
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    _delay_us(0.025); // Delay 25nS for setup time of shift register

    // Rising edge on latch, delay and drop
    PORTB |= (1<<PB2);
    _delay_us(0.025); // Delay 25nS for setup time of shift register
    PORTB &= ~(1<<PB2);
}

ISR(ADC_vect) {
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
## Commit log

2013-11-04 added system diagram
2013-11-19 moved file path
2013-11-19 added usb system
2013-11-30 Started prelim motherboard design.
2013-12-02 updated mobo sch
2013-12-02 added datasheet for mcu
2013-12-02 added usb hub component datasheet
2013-12-02 replicated h-bridges, added usb chip
2013-12-02 usb components
2013-12-07 replacing usb enabled uC with two chip solution
2013-12-08 added new uc and ftdi datasheet
2013-12-08 updated datasheet
2013-12-08 added usb/ttl
2013-12-09 rearranged some signals, corrected cap values
2013-12-09 working on conductivity sensor circuit
2013-12-09 reorganized analog sensor
2013-12-10 added thermal sensors, external switches
2013-12-15 fixed conductivity circuit, connected agnd->gnd
2013-12-21 3.3v regulator datasheet added
2013-12-21 validating subcomponents
2013-12-22 added hbridge datasheet
2013-12-24 finished subsystem validatation
2013-12-25 updated system diagram
2013-12-25 updated sch
2013-12-29 started pcb with initial measurments
2013-12-29 image of sch
2013-12-31 laying out subsystems
2014-01-03 added missing reset capacitor
2014-01-10 rewired h-bridges to not short out and simplified trace layout
2014-01-13 added current liminting resistors to shift registers
2014-01-14 laying out protection diodes
2014-01-14 added bill of materials
2014-01-15 making BOM
2014-01-15 laying out hbridges
2014-01-15 added more bom part numbers
2014-01-16 working on BOM
2014-01-17 worked on BOM
2014-01-17 laying out components
2014-01-18 changing h bridge layout
2014-01-19 layed out hbridges, MCU, new fuses
2014-01-19 updated image
2014-01-21 positioned all but mcu
2014-01-21 putting things into place
2014-01-21 layed out control lines to hbridges, fets
2014-01-22 moved in risers
2014-01-22 moved ruler
2014-01-26 laying out mcu
2014-01-26 still
2014-01-27 finished initial routing
2014-01-27 updated sch/brd images
2014-01-27 finished silkscreen
2014-01-27 added bw footprint image
2014-01-28 corrected and checked BOM
2014-01-28 added excell bom list for budget expantion
2014-01-29 added digikey order summary
2014-01-29 creating production gerber layout
2014-01-29 last changes to motherboard
2014-01-29 started correcting CAM errors on motherboard directly
2014-01-29 corrected drc errors except overlap under 5v buck
2014-01-29 added corrected motherboard to production board
2014-01-29 finished production board design
2014-01-30 final changes to boards for production
2014-01-30 tweaks to boards
2014-01-30 added gerber zip
2014-02-01 started making firmware
2014-02-02 adding modules
2014-02-03 adding new code, created some modules
2014-02-04 working on adc
2014-02-05 replaced mcu datasheet with proper version
2014-02-05 adc isr routine
2014-02-10 adc module done
2014-02-10 uart module done
2014-02-10 uart modlue done
2014-02-10 working on main, moved ISRs
2014-02-10 added gitignore
2014-02-10 working on main
2014-02-10 adding command cases
2014-02-10 adding in motor control
2014-02-10 reconfigured motor commands
2014-02-10 correcting bitfields
2014-02-11 adding temp and current code
2014-02-11 finished adc
2014-02-11 finished uart
2014-02-11 finish spi
2014-02-11 fixed typedefs causing bugs in main
2014-02-11 corrected sources in main
2014-02-11 created procol sheet
2014-02-12 working
2014-02-15 fixed errors from unclosed if/else's, fixed warning in uart clockrate define
2014-02-23 altered for stk500 programming (unproven) and added in ascii debug
2014-02-24 added dead recon mode, debug mode, fixed motor control error, proved system
2014-04-17 tested, things are working
2014-04-23 switched to new programmer
2014-04-23 still working on string tx issue
2014-04-23 should work for pool test
2014-04-27 added directional control system for WASD keys
2014-04-28 updated SID
2014-05-07 final define changes to reverse backwards motors
2015-11-22 removing cruft
2015-11-22 moved everything to hardware folder
2015-11-22 moved files to firmware folder
2015-11-22 moved protocol documentation to folder
2015-11-22 added readme

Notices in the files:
parts and their libraries:
sparkfun: Licensing: CC v3.0 Share-Alike You are welcome to use this library for commercial purposes.
